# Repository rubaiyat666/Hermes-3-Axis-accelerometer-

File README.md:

# Hermes-6-Axis-accelerometer

Hermes is a 6-Axis accelerometer that uses an embeded mpu6050 for controlling and gyro sensing. It has a Xiao RP2040 as a micro controller for it's compact size and versatile use.Designed for real-time motion data visualization in a small, badge-friendly form factor. It's intended use could be in a bicycle or any other device that's position and gyro data needs to be mesured.This is made in kicad and the files needed can be found in this directory. 

## Features

- **MPU-6050 IMU** — 6-axis accelerometer + gyroscope over I2C for
  real-time motion and orientation tracking
- **1.28" I2C OLED Display** — 128×64 pixel screen for live data
  readout or custom graphics
- **Seeed XIAO RP2040** — powerful dual-core microcontroller with
  USB-C, onboard RGB LED, and a tiny footprint
- **Decoupling & Filtering** — on-board bypass capacitors (0.1µF,
  10nF, 2.2nF) for clean, stable power to both ICs
- **Compact PCB Design** — rounded corners, mounting holes, and a
  clean layout with all components on a single board
- **USB-C Powered** — program and power the board directly via the
  XIAO's USB-C port

## BOM

| Name | Purpose | Qty | Total Cost (USD) | Distributor | Link |
|------|---------|-----|-----------------|-------------|------|
| PCB | The board | 5 | $30.00 | JLCPCB | [link](https://jlcpcb.com) |
| 4.7kΩ Resistor | I2C Pull-up | 2 | $1.00 | Digikey | [link](https://www.digikey.com/en/products/detail/susumu/RG2012L-472-L-T05/3738065) |
| 10nF Capacitor | Voltage stabilization | 1 | $1.00 | Digikey | [link](https://www.digikey.com/en/products/detail/kemet/C0402C103K5RECAUTO/8646477) |
| 2.2nF Capacitor | Voltage stabilization | 1 | $1.00 | Digikey | [link](https://www.digikey.com/en/products/detail/kemet/C0402C222F3GECTU/8644380) |
| 0.1µF Capacitor | Voltage stabilization | 2 | $3.00 | Digikey | [link](https://www.digikey.com/en/products/detail/samsung-electro-mechanics/CL05B104KP5NNNC/3886660) |
| 1.3" OLED Display | Output display | 1 | $5.00 | Daraz | [link](https://www.aliexpress.com/item/1005004131362533.html?spm=a2g0o.cart.0.0.7d0b38daOzt1YF&mp=1&pdp_npi=6%40dis%21USD%21USD%203.19%21USD%202.39%21%21USD%202.39%21%21%21%402101246417804712022741622eec63%2112000028137900082%21ct%21BD%217350065947%21%211%210%21&pdp_ext_f=%7B%22cart2PdpParams%22%3A%7B%22pdpBusinessMode%22%3A%22retail%22%7D%7D) |
| Seeed XIAO RP2040 | MCU | 1 | $11.00 | Daraz | [link](https://www.aliexpress.com/item/1005009606027401.html?spm=a2g0o.cart.0.0.ff2038dandQAX1&mp=1&pdp_npi=6%40dis%21USD%21USD+8.00%21USD+8.00%21%21USD+8.00%21%21%21%402101246417804709802308374eec63%2112000049609674780%21ct%21BD%217350065947%21%211%210%21) |
| MPU-6050 | Accelerometer/Gyroscope | 1 | $14.90 | TDK InvenSense | [link](https://jlcpcb.com/partdetail/TDKInvenSense-MPU6050/C24112) |

**Total Estimated Cost: $66.90**

Made by  </>RUBAIYAT

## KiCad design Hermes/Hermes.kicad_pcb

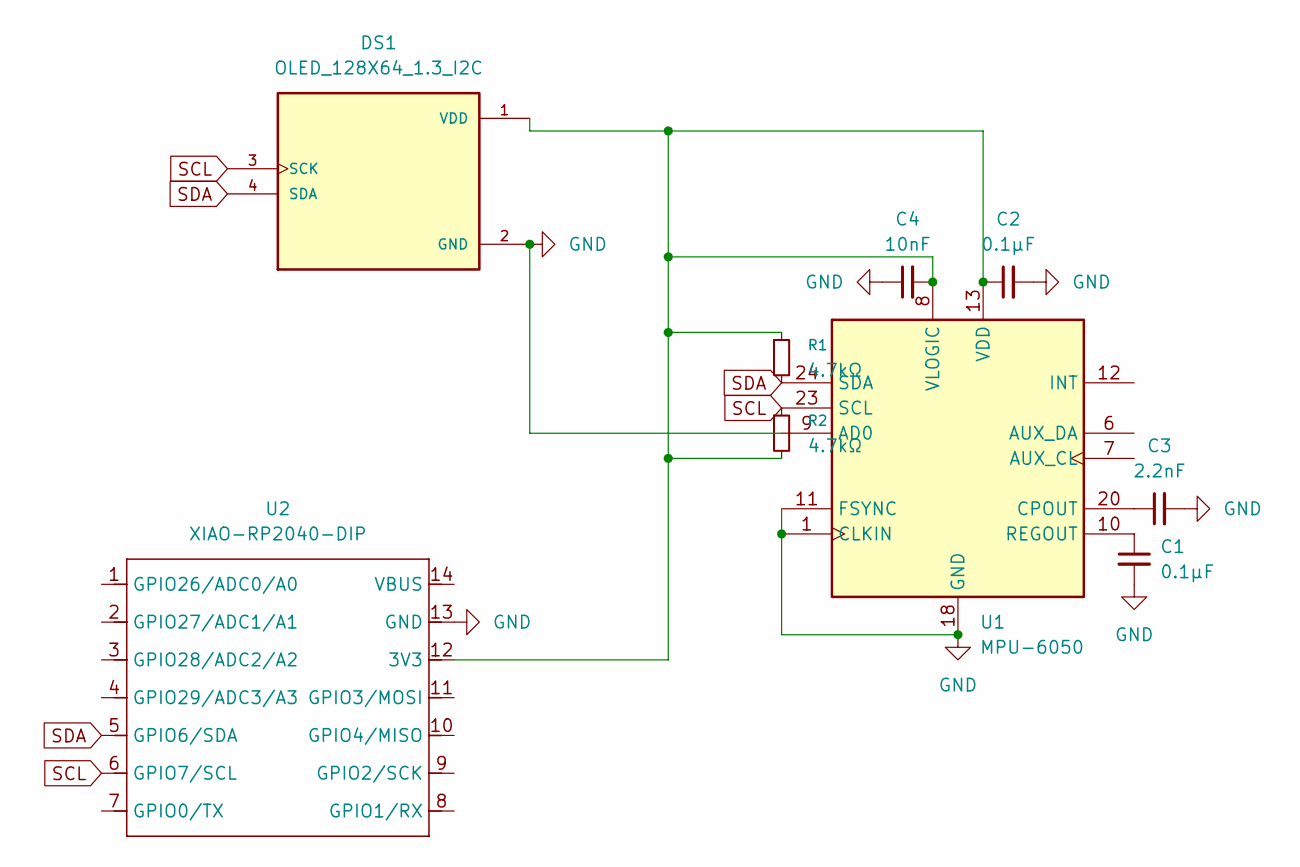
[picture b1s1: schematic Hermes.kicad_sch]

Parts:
C1, C2: 0.1µF; C_0402_1005Metric
C3: 2.2nF; C_0402_1005Metric
C4: 10nF; C_0402_1005Metric
DS1: OLED_128X64_1.3_I2C; LCD_OLED_128X64_1.3_I2C; PARTREV NA
R1, R2: 4.7kΩ; R_0402_1005Metric
U1: MPU-6050; InvenSense_QFN-24_4x4mm_P0.5mm
U2: XIAO-RP2040-DIP

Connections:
GND: C1.2, C2.2, C3.2, C4.1, DS1.2 (GND), U1.1 (CLKIN), U1.9 (AD0), U1.11 (FSYNC), U1.18 (GND), U2.13 (GND)
unnamed: C2.1, C4.2, DS1.1 (VDD), R1.1, R2.2, U1.8 (VLOGIC), U1.13 (VDD), U2.12 (3V3)
unnamed: C3.1, U1.20 (CPOUT)
unnamed: C1.1, U1.10 (REGOUT)
SCL: DS1.3 (SCK), R2.1, U1.23 (SCL), U2.6 (GPIO7/SCL)
SDA: DS1.4 (SDA), R1.2, U1.24 (SDA), U2.5 (GPIO6/SDA)

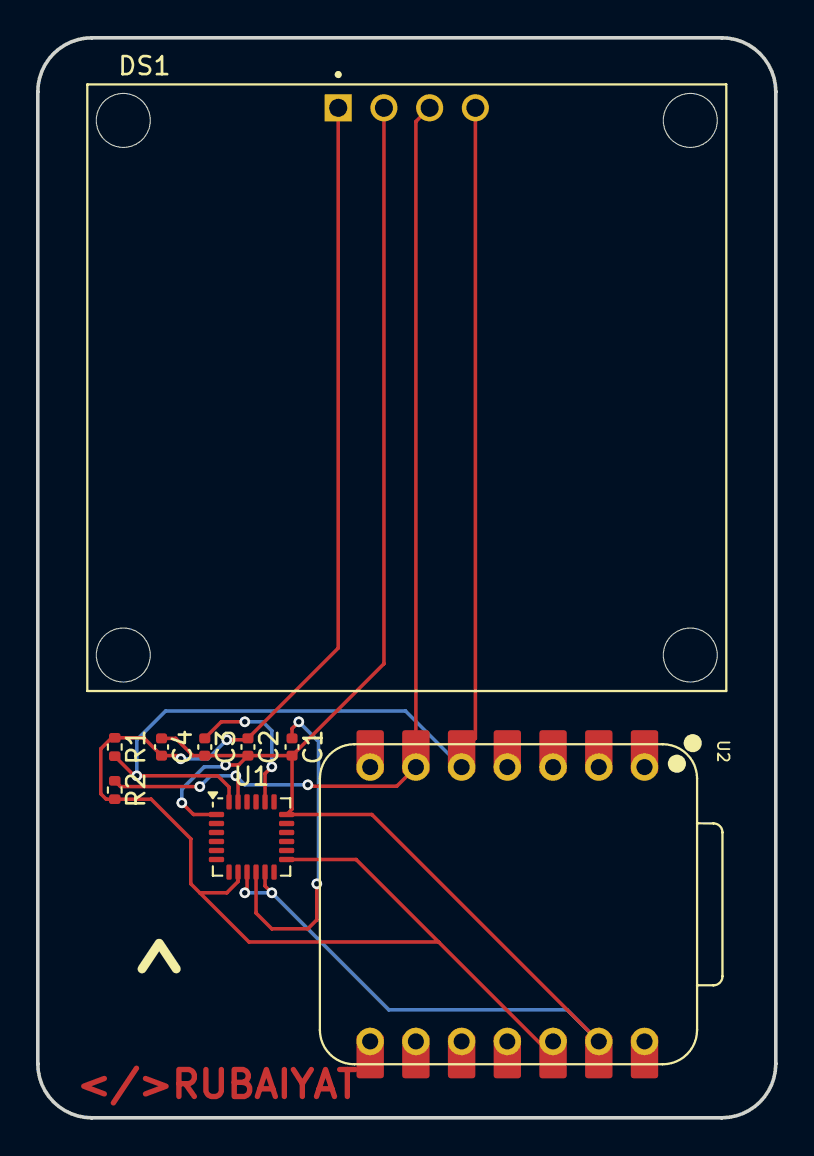
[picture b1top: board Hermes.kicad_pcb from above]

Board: 2 copper layers, 41.0 x 60.0 mm, 9 parts (0 on the bottom side), 6 nets.

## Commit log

2026-06-03 Update README to reflect 6-Axis accelerometer
